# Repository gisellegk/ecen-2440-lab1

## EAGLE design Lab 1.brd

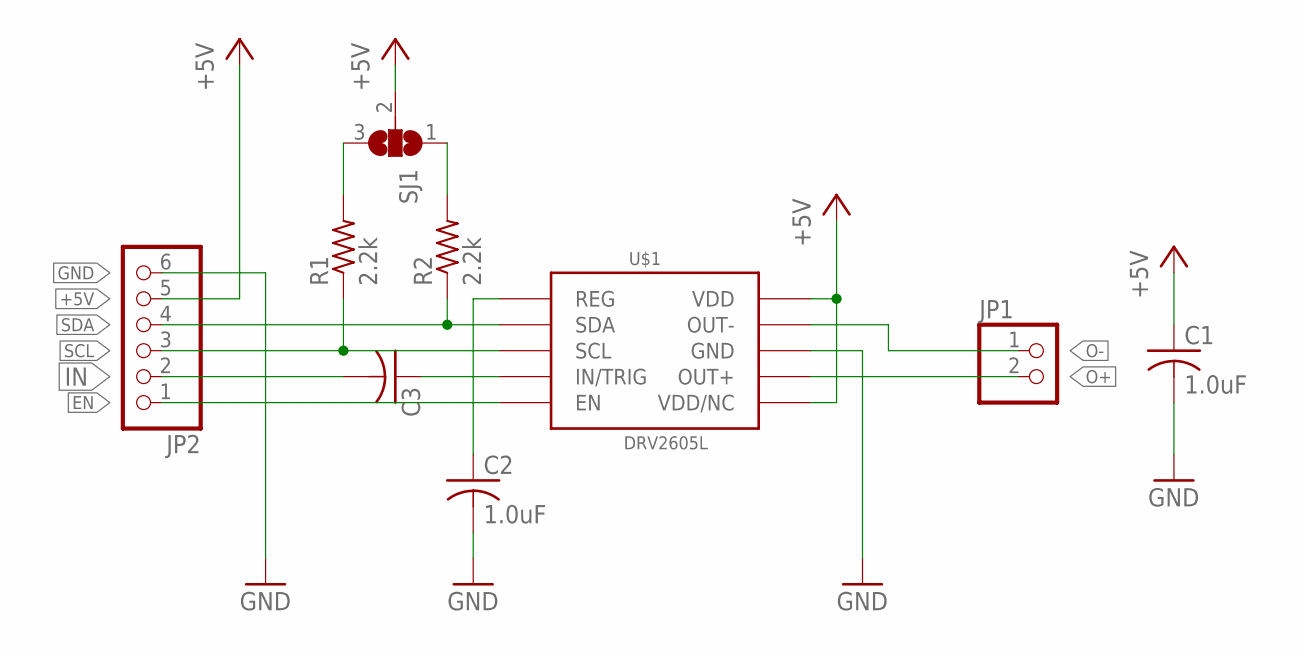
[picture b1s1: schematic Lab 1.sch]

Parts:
C1, C2: 1.0uF; C0805
C3: C-USC0805; C0805
JP1: PINHD-1X2; 1X02
JP2: PINHD-1X6; 1X06
R1, R2: 2.2k; R0805
SJ1: SJ2W; SJ_2
U$1: DRV2605L; VSSOP-10

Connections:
+5V: C1.1, JP2.5, SJ1.2, U$1.P$6 (VDD/NC), U$1.P$10 (VDD)
EN: JP2.1, U$1.P$5 (EN)
GND: C1.2, C2.2, JP2.6, U$1.P$8 (GND)
IN: C3.2, JP2.2
unnamed: C3.1, U$1.P$4 (IN/TRIG)
unnamed: R1.2, SJ1.3
unnamed: R2.2, SJ1.1
unnamed: C2.1, U$1.P$1 (REG)
O+: JP1.2, U$1.P$7 (OUT+)
O-: JP1.1, U$1.P$9 (OUT-)
SCL: JP2.3, R1.1, U$1.P$2 (SCL)
SDA: JP2.4, R2.1, U$1.P$3 (SDA)

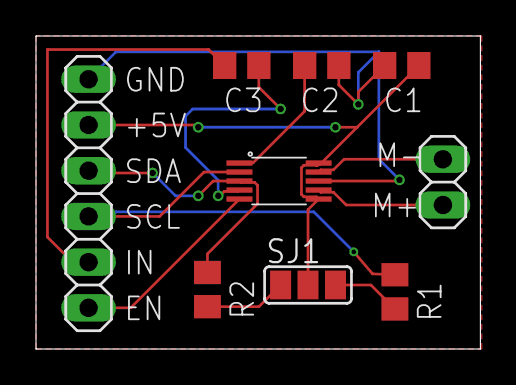
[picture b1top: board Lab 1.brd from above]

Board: 2 copper layers, 24.7 x 17.4 mm, 9 parts (0 on the bottom side), 12 nets.

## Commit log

2019-09-04 hello world
2019-09-04 gitignore
2019-09-04 ripup
2019-09-05 Added Ground Plane. Added Filter Capacitor
2019-09-07 Updated: Sep 6

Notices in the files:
parts and their libraries:
SparkFun-IC-Special-Function: Licensing: Creative Commons ShareAlike 4.0 International - https://creativecommons.org/licenses/by-sa/4.0
